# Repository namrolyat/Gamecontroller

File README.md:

# Gamecontroller
Gamecontroller with Teensy LC en Arduino Leonardo.
To sent 7 different CHAR to the PC like a keyboard HID.
Example Q,W,E,R,T,Y  or 1234567 enz....
For the second time!!

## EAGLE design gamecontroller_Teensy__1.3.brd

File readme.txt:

Ga naar http://www.arduino.cc/en/Guide/Libraries voor meer informatie over het installeren van bibliotheken
dit is een test voor github 
Robert D'Arcangelo
test nummer 3

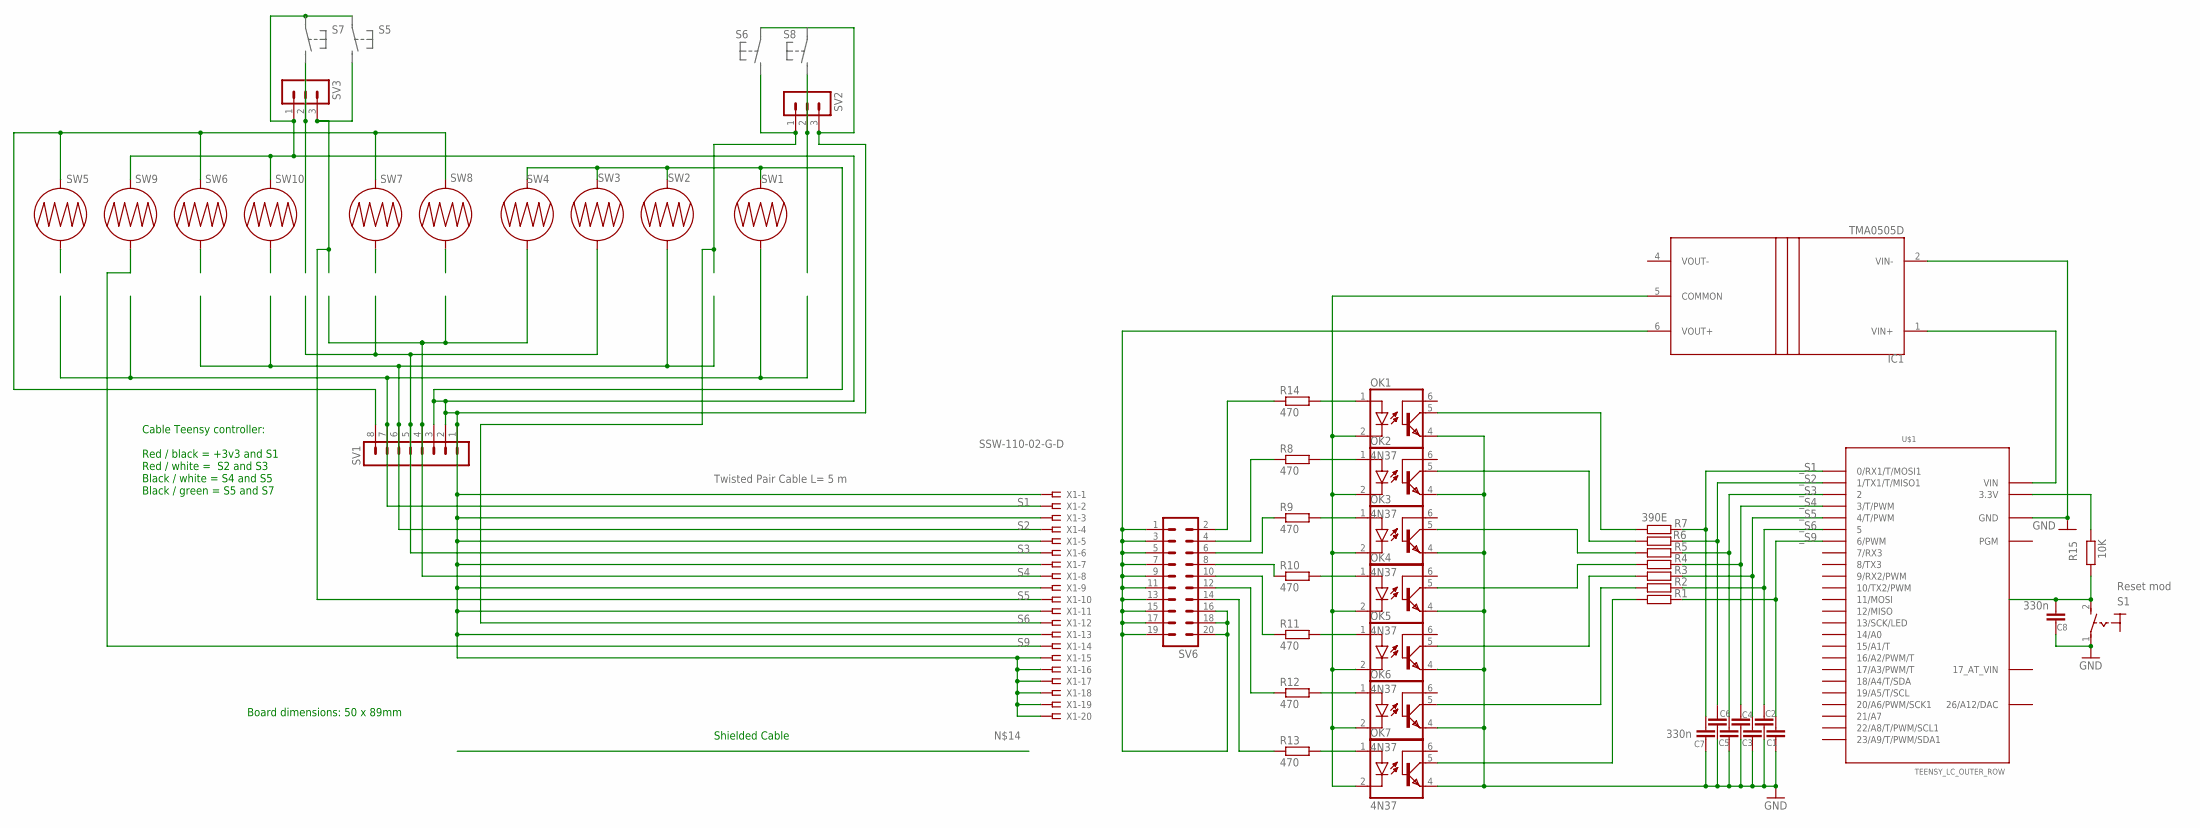
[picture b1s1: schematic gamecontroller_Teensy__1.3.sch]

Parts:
C1, C2, C3, C4, C5, C6: C-EU025-025X050; C025-025X050
C7, C8: 330n; C025-025X050
IC1: TMA0505D; SIP7
OK1, OK2, OK3, OK4, OK5, OK6, OK7: 4N37; DIL06
R1, R2, R3, R4, R5, R6: R-EU_0204/5; 0204/5
R7: 390E; 0204/5
R8, R9, R10, R11, R12, R13, R14: 470; 0204/5
R15: 10K; 0204/5
S1: Reset mod; MS243
SV1: MA08-1
SV2, SV3: MA03-1
SV6: MA10-2W
SW1, SW2, SW3, SW4, SW5, SW6, SW7, SW8, SW9, SW10: BUTTON-CONDUCTIVESMD-0.1"; BUTTON-CONDUCTIVE-0.1
U$1: TEENSY_LC_OUTER_ROW; TEENSY_3.0-3.2&LC_OUTER_ROW
X1: SSW-110-02-G-D

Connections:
26/A12/DAC: U$1.RESET/DAC (26/A12/DAC)
COMMON: SV1.1, SV1.2, SV1.3, SV2.3, SV3.1, SW1.2, SW2.2, SW3.2, SW4.2, SW9.1, SW10.1, X1.1, X1.3, X1.5, X1.7, X1.9, X1.11, X1.13, X1.15, X1.16, X1.17, X1.18, X1.19, X1.20
GND: C1.2, C2.2, C3.2, C4.2, C5.2, C6.2, C7.2, C8.2, IC1.2 (VIN-), OK1.4 (EMI), OK2.4 (EMI), OK3.4 (EMI), OK4.4 (EMI), OK5.4 (EMI), OK6.4 (EMI), OK7.4 (EMI), S1.1, U$1.AGND (GND), U$1.GND, U$1.GND1 (GND)
unnamed: R8.1, SV6.4
unnamed: OK1.1 (A), R14.2
unnamed: SV1.8, SW5.1, SW6.1, SW7.1, SW8.1
unnamed: R14.1, SV6.2
unnamed: IC1.6 (VOUT+), SV6.1, SV6.3, SV6.5, SV6.7, SV6.9, SV6.11, SV6.13, SV6.15, SV6.16, SV6.17, SV6.18, SV6.19, SV6.20
unnamed: OK1.5 (COL), R7.1
unnamed: R9.1, SV6.6
unnamed: R10.1, SV6.8
unnamed: R11.1, SV6.10
unnamed: R12.1, SV6.12
unnamed: OK2.5 (COL), R6.1
unnamed: OK3.5 (COL), R5.1
unnamed: OK4.5 (COL), R4.1
unnamed: OK5.5 (COL), R3.1
unnamed: OK6.5 (COL), R2.1
unnamed: OK7.5 (COL), R1.1
unnamed: OK2.1 (A), R8.2
unnamed: OK3.1 (A), R9.2
unnamed: OK4.1 (A), R10.2
unnamed: C8.1, R15.1, S1.2 (S)
unnamed: R13.1, SV6.14
unnamed: OK7.1 (A), R13.2
unnamed: OK6.1 (A), R12.2
unnamed: OK5.1 (A), R11.2
unnamed: IC1.1 (VIN+), U$1.VIN
unnamed: R15.2, U$1.3.3V, U$1.3.3V1 (3.3V)
unnamed: IC1.5 (COMMON), OK1.2 (C), OK2.2 (C), OK3.2 (C), OK4.2 (C), OK5.2 (C), OK6.2 (C), OK7.2 (C)
S1: SV1.7, SW1.1, X1.2
S2: SV1.6, SW2.1, X1.4
S3: SV1.5, SW3.1, X1.6
S4: SV1.4, SW4.1, X1.8
S5: SV3.3, X1.10
S6: SV2.1, X1.12
S9: SW9.2, X1.14
VOUT-: IC1.4 (VOUT-)
_S1: C7.1, R7.2, U$1.0 (0/RX1/T/MOSI1)
_S2: C6.1, R6.2, U$1.1 (1/TX1/T/MISO1)
_S3: C5.1, R5.2, U$1.2
_S4: C4.1, R4.2, U$1.3 (3/T/PWM)
_S5: C3.1, R3.2, U$1.4 (4/T/PWM)
_S6: C2.1, R2.2, U$1.5
_S9: C1.1, R1.2, U$1.6 (6/PWM)

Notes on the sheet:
Board dimensions: 50 x 89mm
Shielded Cable
Twisted Pair Cable L= 5 m
Cable Teensy controller: Red / black = +3v3 and S1 Red / white = S2 and S3 Black / white = S4 and S5 Black / green = S5 and S7

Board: 2 copper layers, 48 parts (0 on the bottom side), 43 nets, no tracks yet.

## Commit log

2020-10-08 Update README.md
    Arduino leonardo toegevoegd
2020-10-08 Add files via upload
    Arduino file geupload van bedcontroller
2020-10-08 Add files via upload
    test text file
2020-10-08 Update readme.txt
    tekst toegevoegd aan txt file
2020-10-08 Update readme.txt
    text toegevoegd.
2020-10-09 info toegevoegd
    info over het doel van de controllers toegevoegd.
2020-10-09 Add files via upload
    Word doc with all the info about the project.
2020-10-09 Add files via upload
    Arduino file for the Leonardo or Micro.
2020-10-09 Add files via upload
    Code for the Teensy LC
2020-10-09 Add files via upload
    Picture of the PCB.
2020-10-09 Add files via upload
    Picture off the game controller PCB.
2020-10-09 Add files via upload
    Eagle schematics.
2020-10-09 Add files via upload
    PDF files.
